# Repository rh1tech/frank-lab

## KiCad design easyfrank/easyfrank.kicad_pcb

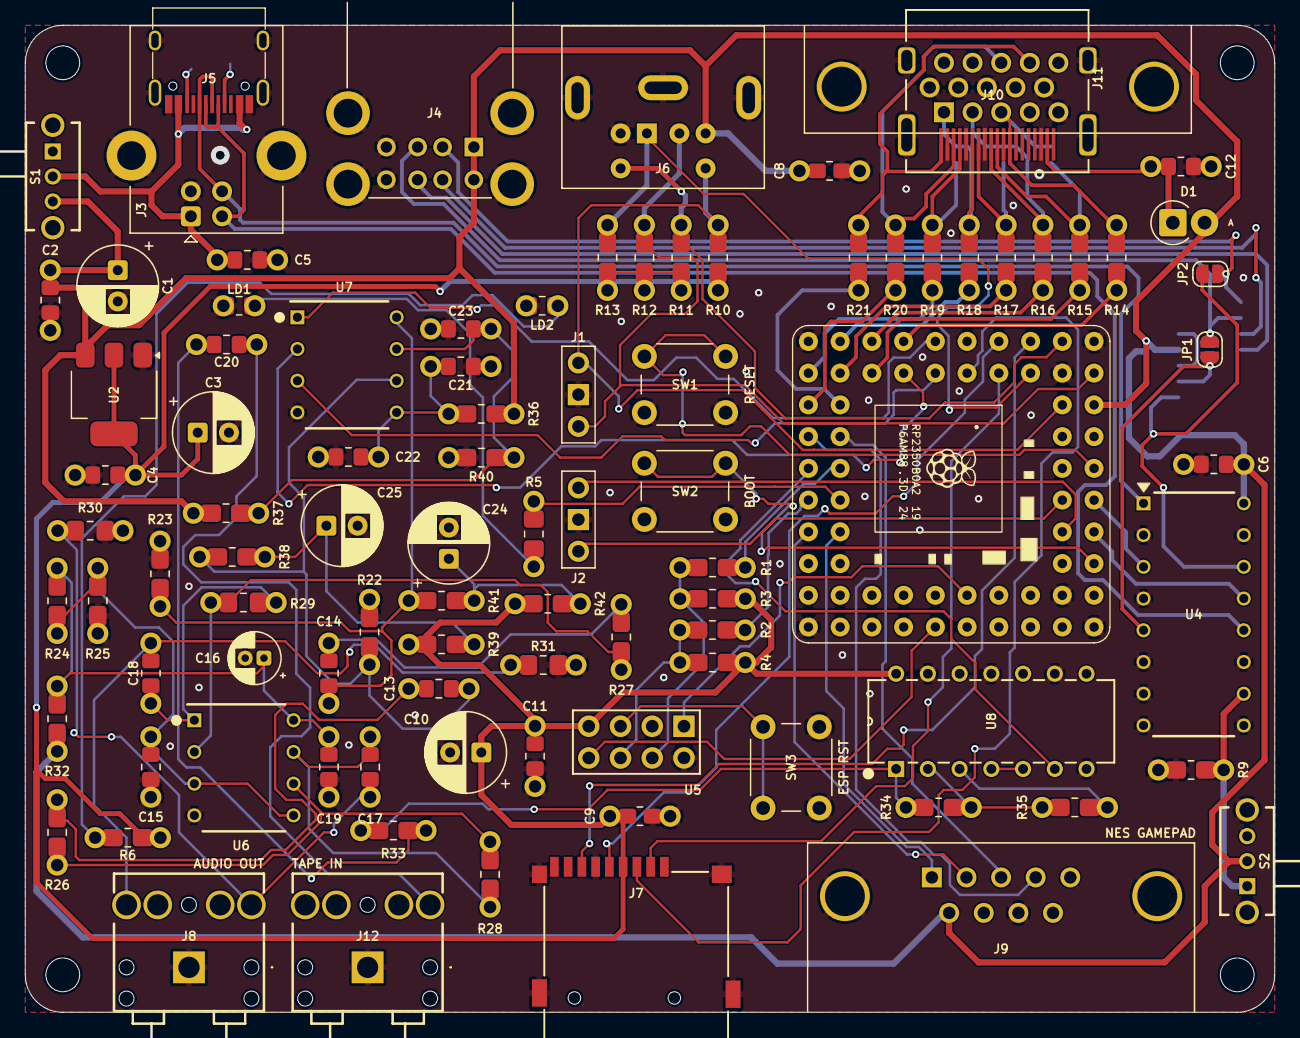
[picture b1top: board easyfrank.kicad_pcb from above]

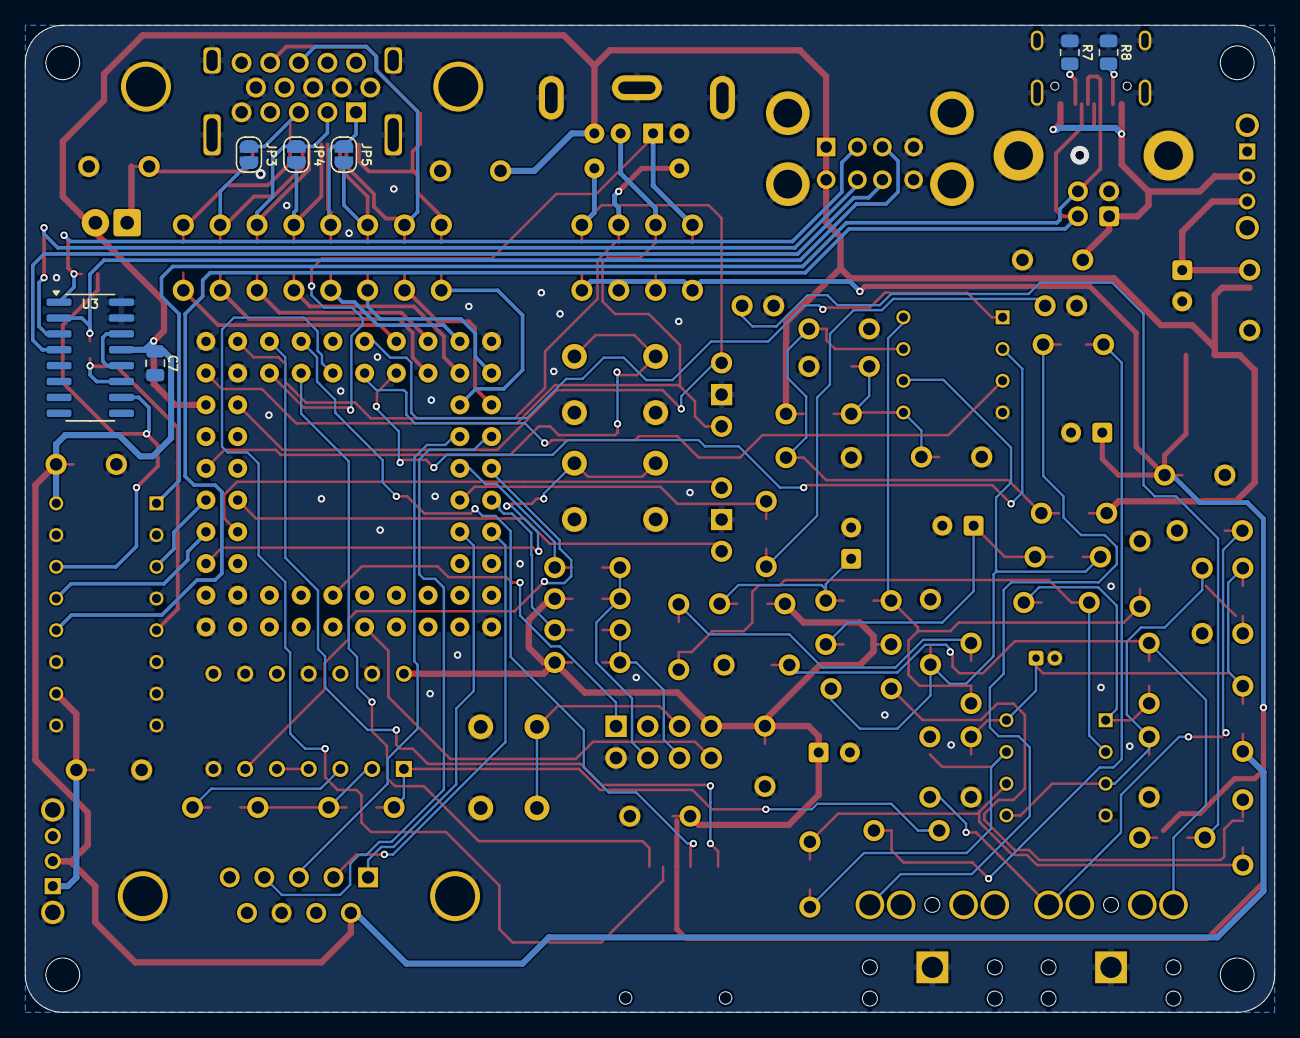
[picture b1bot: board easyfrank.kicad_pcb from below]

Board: 2 copper layers, 100.0 x 79.0 mm, 104 parts (7 on the bottom side), 87 nets.

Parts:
C1, C3, C10, C24, C25: 100u; C_Radial_D6.3mm_P2.50mm
C2, C4, C6, C8, C9, C11, C12, C19, C20, C22: 100n; Combined_0805_CR
C5, C13, C14, C15, C17, C18, C21, C23: 10u; Combined_0805_CR
C7: 4.7u; C_0805_2012Metric
C16: 10u; CP_Radial_D4.0mm_P1.50mm
D1: 1N5819; D_SOD81_P2.54mm_Vertical_AnodeUp
H1, H2, H3, H4: Hole 2.7mm; MountingHole_2.7mm
J1: UART; PinSocket_1x03_P2.54mm_Vertical
J2: Debug; PinSocket_1x03_P2.54mm_Vertical
J3: USB_B; USB_B_Horizontal
J4: SS-52100-004; USB_A_Stacked
J5: USB4215-03-A; USB_C_Receptacle
J6: MDC-036; MiniDIN_6pin_Female
J7: 104031-0811; MicroSD_SMD_Long
J8: SJ1-3525N Green; AudioJack_3.5mm_SJ1-3525N_Green
J9: D-SUB 9 Male; DSUB-9_Male_TopMount
J10: DC3RX19JA2; HDMI_Female
J11: D-SUB 15 Female; DSUB-15_Female
J12: SJ1-3525N Red; AudioJack_3.5mm_SJ1-3525N_Red
JP1, JP2, JP3, JP4, JP5: Jumper (Solder); SolderJumper_2Pin
LD1: Blue; Combined_0805_LED
LD2: Green; Combined_0805_LED
R1, R2, R5, R6, R10, R11, R12, R13: 1K; Combined_0805_RE
R3, R4, R9, R24, R25, R26, R27, R40: 10K; Combined_0805_RE
R7, R8: 5.1K; R_0805_2012Metric
R14, R15, R16, R17, R18, R19, R20, R21: 220R; Combined_0805_RE
R22, R23: 2.2K; Combined_0805_RE
R28, R29: 47K; Combined_0805_RE
R30, R31: 20K; Combined_0805_RE
R32, R36, R39, R42: 100R; Combined_0805_RE
R33: 4.7K; Combined_0805_RE
R34, R35: 100K; Combined_0805_RE
R37: 51K; Combined_0805_RE
R38, R41: 470R; Combined_0805_RE
S1, S2: SK12D07VG3NS; Switch_Slide_SK12D07VG3NS
SW1: Reset; SW_PUSH_6mm_H5mm
SW2: Boot; SW_PUSH_6mm_H5mm
SW3: ESP01 Reset; SW_PUSH_6mm_H5mm
U1: Pimoroni PGA2350; PGA2350
U2: AMS1117-3.3; SOT-223-3_TabPin2
U3: MW7211A; SOP-16_3.9x9.9mm_P1.27mm
U4: 74HC4052; 74HC4052N
U5: ESP-01v090; ESP-01S
U6: LM358; DIP-8_W7.94mm_P2.54mm
U7: TDA1545A; DIP-8_W7.94mm_P2.54mm
U8: CD4069UBE

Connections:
+3V3: C3.1, C4.2, C9.2, C10.1, C11.2, J7.4 (VDD), R3.2, R4.2, R6.2, R10.2, R11.2, R12.2, R13.2, R39.1, R42.1, U2.2 (VO), U5.7 (VCC), U8.14 (VDD)
/Audio/AMP_OUTL: C17.2, J8.2 (TIP), R30.2
/Audio/AMP_OUTR: C18.2, J8.3 (RING), R31.2
/Audio/TDA_L: C13.1, R22.1, R38.2, U7.6 (IOL)
/Audio/TDA_R: C14.1, R23.1, R41.1, U7.8 (IOR)
/CDDAT3/GP5: J7.2 (DAT3/CD), U1.5 (GP5)
/CLKN/GP12: R14.2, U1.12 (GP12)
/CLKP/GP13: R15.2, U1.13 (GP13)
/CLK/GP6: J7.5 (CLK), U1.6 (GP6)
/CMD/GP7: J7.3 (CMD), U1.7 (GP7)
/D0N/GP14: R16.2, U1.14 (GP14)
/D0P/GP15: R17.2, U1.15 (GP15)
/D1N/GP16: R18.2, U1.16 (GP16)
/D1P/GP17: R19.2, U1.17 (GP17)
/D2N/GP18: R20.2, U1.19 (GP18)
/D2P/GP19: R21.2, U1.20 (GP19)
/DAT0/GP4: J7.7 (DAT0), U1.4 (GP4)
/DATA1/GP26: J9.2, U1.27 (GP26)
/DATA2/GP27: J9.1, U1.28 (GP27)
/DM: U1.53 (USB_DM), U4.13 (1Z)
/DP: U1.54 (USB_DP), U4.3 (2Z)
/EGP0/GP24: R2.2, U1.25 (GP24)
/EGP2/GP23: R1.2, U1.24 (GP23)
/ESP01S/GPIO0: R2.1, R4.1, U5.6 (GPIO0)
/ESP01S/GPIO2: R1.1, R3.1, U5.4 (GPIO2)
/J3/GP21: J9.3, U1.22 (GP21)
/J4/GP20: J9.4, U1.21 (GP20)
/KB_CLK/GP2: J6.5, R11.1, U1.2 (GP2)
/KB_DATA/GP3: J6.1, R13.1, U1.3 (GP3)
/LOAD_IN/GP22: U1.23 (GP22), U8.6 (I=*C)
/MS_CLK/GP0: J1.1, J6.6, R10.1, U1.61 (GP0)
/MS_DATA/GP1: J1.3, J6.2, R12.1, U1.62 (GP1)
/PGA2350/BOOTSEL: SW2.1, U1.51 (BOOTSEL)
/PGA2350/RUN: SW1.1, U1.56 (RUN)
/PGA2350/SWCLK: J2.3, U1.55 (SWCLK)
/PGA2350/SWDIO: J2.1, U1.52 (SWDIO)
/RX/GP38: U1.40 (GP38), U5.8 (URXD)
/TDA_DATA/GP9: U1.9 (GP9), U7.3 (DATA)
/TDA_LRCK/GP11: U1.11 (GP11), U7.2 (WS)
/TDA_SCLK/GP10: U1.10 (GP10), U7.1 (BCK)
/TX/GP39: U1.41 (GP39), U5.1 (UTXD)
/Tape In/TAPE: C20.2, J12.2 (TIP)
/USB/DI+: J3.3 (D+), J5.6 (DP1), J5.8 (DP2), U4.1 (2Y0)
/USB/DI-: J3.2 (D-), J5.5 (DN2), J5.7 (DN1), U4.12 (1Y0)
/USB/DS+: JP1.1 (A), U3.11 (DPU), U4.5 (2Y1)
/USB/DS-: JP2.1 (A), U3.10 (DMU), U4.14 (1Y1)
/USB/DU1+: J4.3 (D1+), JP1.2 (B), U3.2 (DP0)
/USB/DU1-: J4.2 (D1-), JP2.2 (B), U3.1 (DM0)
/USB/DU2+: J4.7 (D2+), U3.4 (DP1)
/USB/DU2-: J4.6 (D2-), U3.3 (DM1)
/USB/VBUS_IN: C5.1, J3.1 (VBUS), J5.2 (VBUS), J5.11 (VBUS), S1.2
/Video Out/VGA_B: J10.12 (CLKN), J11.3, JP3.1 (A), R14.1
/Video Out/VGA_BH: J10.10 (CLKP), JP3.2 (B), R15.1
/Video Out/VGA_G: J10.9 (D0N), J11.2, JP4.1 (A), R16.1
/Video Out/VGA_GH: J10.7 (D0P), JP4.2 (B), R17.1
/Video Out/VGA_HS: J10.3 (D2N), J11.13, R20.1
/Video Out/VGA_R: J10.6 (D1N), J11.1, JP5.1 (A), R18.1
/Video Out/VGA_RH: J10.4 (D1P), JP5.2 (B), R19.1
/Video Out/VGA_VS: J10.1 (D2P), J11.14, R21.1
GND: C1.2, C2.1, C3.2, C4.1, C5.2, C6.1, C7.2, C8.2, C9.1, C10.2, C11.1, C12.2, C15.1, C16.2, C19.1, C21.2, C22.2, C23.1, C24.2, C25.2, J1.2, J2.2, J3.4 (GND), J3.SH (Shield), J4.4 (GND1), J4.8 (GND2), J4.SH (Shield), J5.1 (GND), J5.12 (GND), J5.13 (SHIELD), J6.3, J7.6 (VSS), J8.1 (SLEEVE), J9.8, J10.2 (G_D2), J10.5 (G_D1), J10.8 (G_D0), J10.11 (G_CLK), J10.17 (G_DDC/CEC), J10.20 (SHIELD1), J10.21 (SHIELD2), J10.22 (SHIELD3), J10.23 (SHIELD4), J11.0, J11.5, J11.6, J11.7, J11.8, J11.10, J12.1 (SLEEVE), LD1.1 (K), LD2.1 (K), R7.1, R8.1, R9.1, R22.2, R23.2, R25.1, R30.1, R31.1, R40.1, S2.4 (MH1), S2.5 (MH2), SW1.2, SW2.2, SW3.2, U1.1 (GND), U1.18 (GND), U1.33 (GND), U1.48 (GND), U2.1 (GND), U3.15 (GND), U3.16 (GND), U4.2 (2Y2), U4.4 (2Y3), U4.6 (~E), U4.7 (VEE), U4.8 (GND), U4.9 (S1), U4.11 (1Y3), U4.15 (1Y2), U5.2 (GND), U6.4 (V-), U7.4 (GND), U8.7 (VSS), U8.9 (D14), U8.11 (E), U8.13 (F)
GP25: R5.2, U1.26 (GP25)
unnamed: C13.2, R26.2
unnamed: C14.2, R27.2
unnamed: C17.1, R28.1, U6.7
unnamed: C18.1, R29.1, U6.1
unnamed: C20.1, R33.2
unnamed: C24.1, R41.2, R42.2
unnamed: C25.1, R38.1, R39.2
unnamed: C12.1, D1.1 (K), J10.18 (+5V)
unnamed: J5.4 (CC1), R7.2
unnamed: J5.10 (CC2), R8.2
unnamed: LD1.2 (A), R5.1
unnamed: LD2.2 (A), R6.1
unnamed: U3.12 (VD33), U3.14 (VD3)
unnamed: R9.2, S2.1, U4.10 (S0)
unnamed: SW3.1, U5.5 (RST)
unnamed: C15.2, R24.1, R25.2, U6.3 (+), U6.5 (+)
unnamed: R27.1, R29.2, U6.2 (-)
unnamed: R26.1, R28.2, U6.6 (-)
unnamed: C16.1, C19.2, R24.2, R32.2, U6.8 (V+)
unnamed: C23.2, R37.2, R40.2, U7.7 (IREF)
unnamed: C21.1, C22.1, R36.1, U7.5 (VDD)
unnamed: R33.1, R34.2, U8.1 (A)
unnamed: R35.1, U8.3 (B)
unnamed: U8.4 (H=*B), U8.5 (C)
unnamed: R34.1, R35.2, U8.2 (G-*A)
VBUS: C1.1, C2.2, C6.2, C7.1, C8.1, D1.2 (A), J4.1 (VBUS1), J4.5 (VBUS2), J6.4, J9.6, R32.1, R36.2, R37.1, S1.3, S2.2, U1.60 (VBUS), U2.3 (VI), U3.13 (VDD5), U4.16 (VCC)

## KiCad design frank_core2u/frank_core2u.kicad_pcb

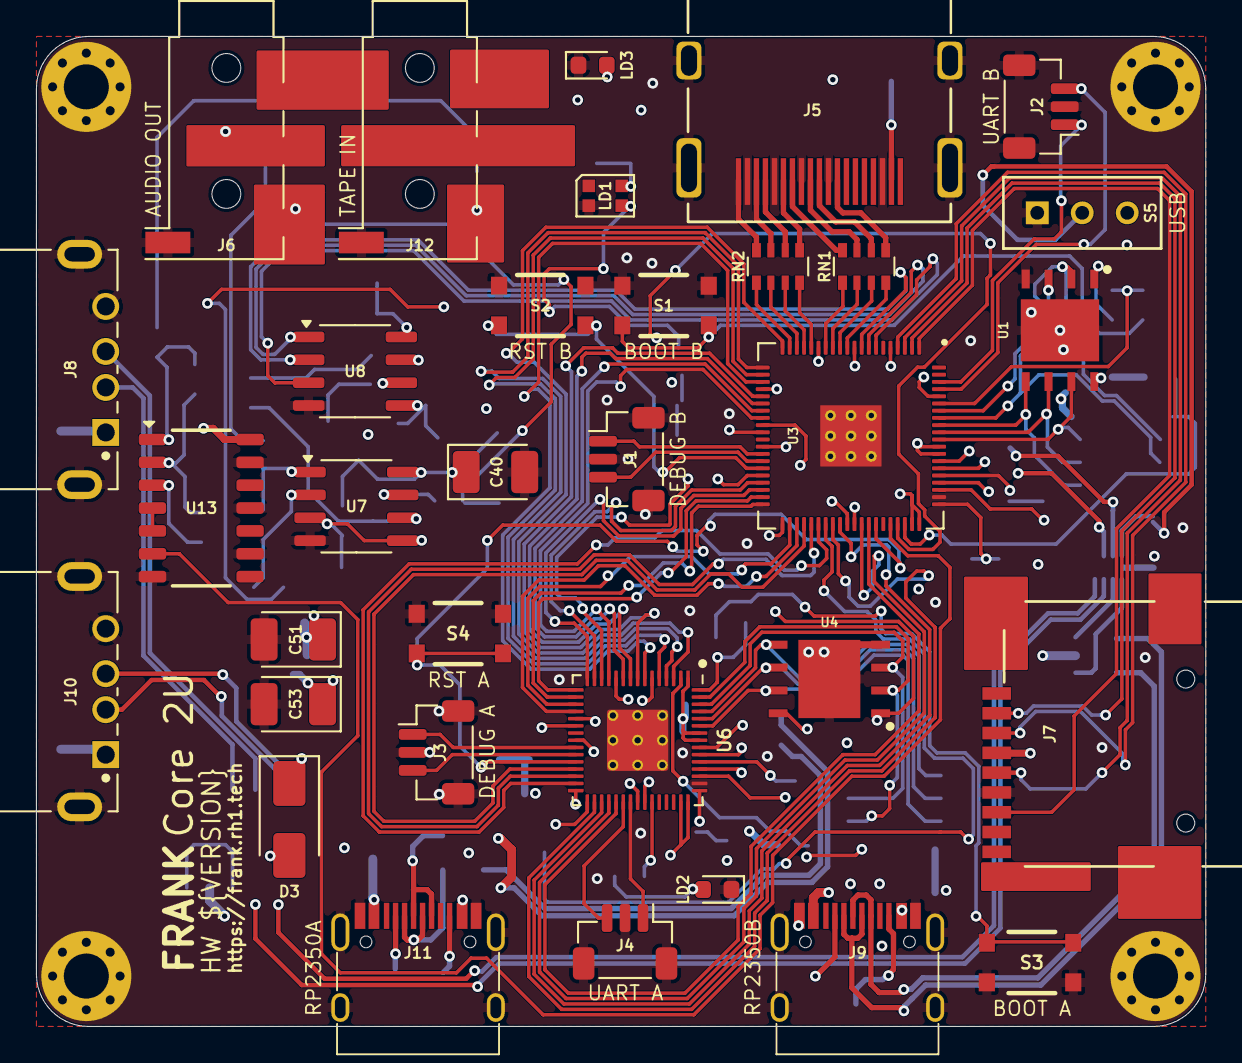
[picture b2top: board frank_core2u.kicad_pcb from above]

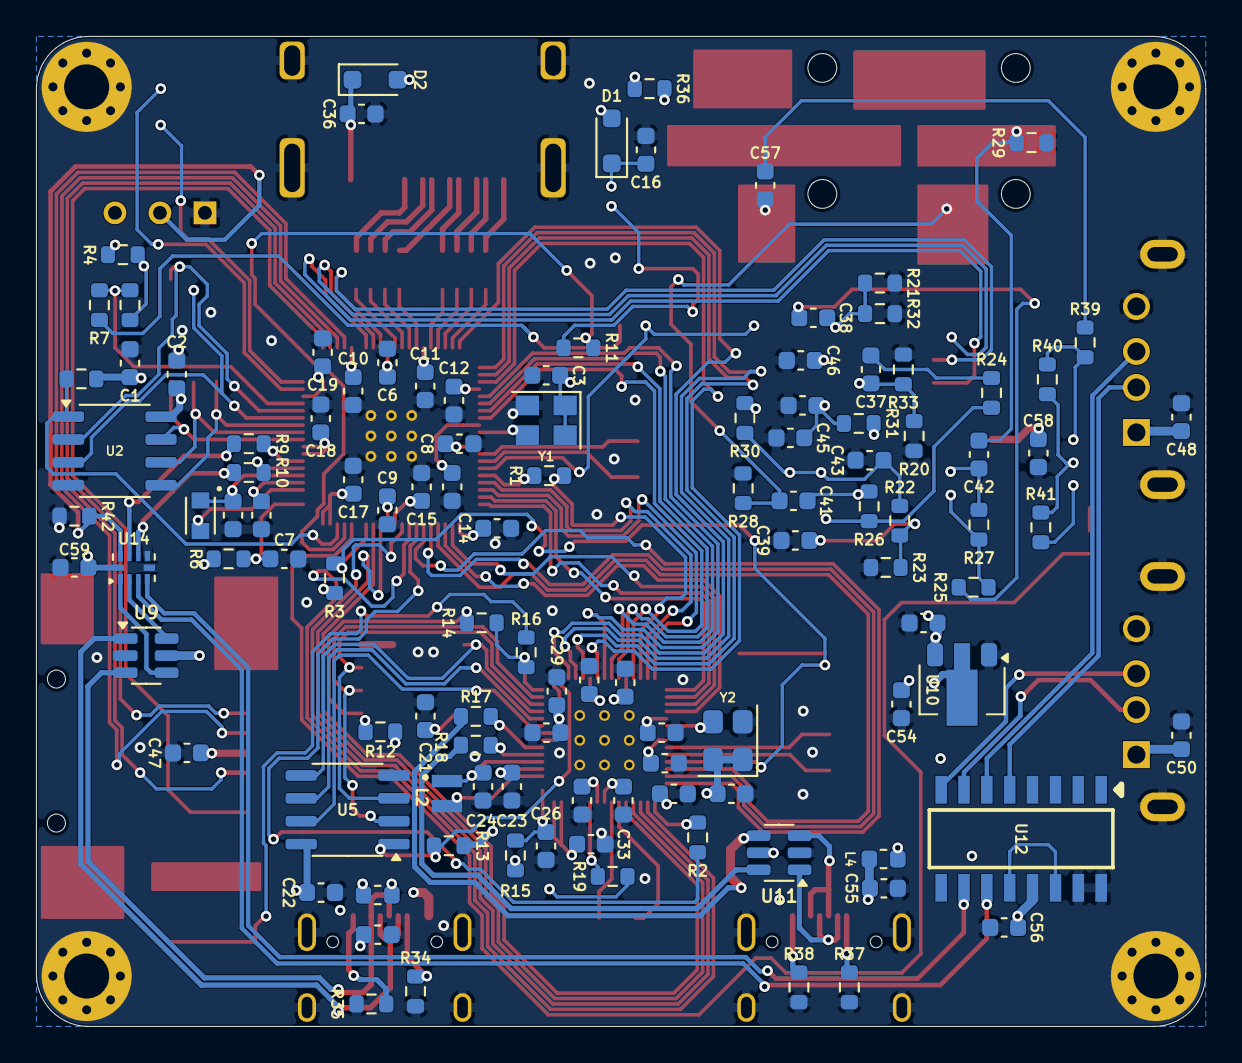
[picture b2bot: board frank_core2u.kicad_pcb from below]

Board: 4 copper layers, 65.0 x 55.0 mm, 150 parts (113 on the bottom side), 144 nets.

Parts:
C1, C2, C3, C6, C9, C10, C11, C12, C13, C14, C15, C16, C17, C18, C19, C20, C21, C22, C25, C28, C29, C30, C31, C32, C33, C34, C35, C36, C43, C45, C47, C48, C49, C50, C52, C54, C55, C59: 100n; C_0603_1608Metric
C4, C5, C7, C8, C23, C24, C26, C27, C56: 4.7u; C_0603_1608Metric
C37, C38, C39, C41, C42, C44, C46: 10u; C_0603_1608Metric
C40: 10u; CP_EIA-3528-12_Kemet-T
C51, C53: 22u; CP_EIA-3528-12_Kemet-T
C57, C58: 100nF; C_0603_1608Metric
D1, D2: 1N5819WS; D_SOD-323
D3: SS34; D_SMA
H1, H2, H3, H4: MountingHole; MountingHole_2.5mm_Pad_Via
J1, J3: Debug; JST_SH_1x03_P1.00mm_Vertical
J2, J4: UART; JST_SH_1x03_P1.00mm_Vertical
J5: DC3RX19JA2; HDMI_Female
J6: PJ-320D; AudioJack_3.5mm_PJ320D_AudioOut
J7: 104031-0811; MicroSD_SMD_Long
J8, J10: 676430910; USB_A_Short
J9, J11: USB4215-03-A; USB_C_Receptacle
J12: PJ-320D; AudioJack_3.5mm_PJ320D_TapeIn
L1: 3.3u; L_Murata_LQH2MCN_2.0x1.6mm
L2: 3.3u; L_AOTA-B201610_2.0x1.6mm
L3, L4: 330R; L_0603_1608Metric
LD1: WS2812B-2020; LED_WS2812B-2020_PLCC4_2.0x2.0mm
LD2: Blue; LED_0603_1608Metric
LD3: Green; LED_0603_1608Metric
R1, R2, R6, R15: 33R; R_0603_1608Metric
R3, R4, R5, R12, R13, R20, R21, R22, R23, R24, R25, R42: 10K; R_0603_1608Metric
R7, R16, R19, R36: 1K; R_0603_1608Metric
R8, R14: 0R; R_0603_1608Metric
R9, R10, R17, R18: 27R; R_0603_1608Metric
R11: 330R; R_0603_1608Metric
R26, R27: 47K; R_0603_1608Metric
R28, R29: 20K; R_0603_1608Metric
R30, R31: 100R; R_0603_1608Metric
R32, R33: 470R; R_0603_1608Metric
R34, R35, R37, R38: 5.1K; R_0603_1608Metric
R39: 4.7K; R_0603_1608Metric
R40, R41: 100K; R_0603_1608Metric
RN1, RN2: 270R; R_Array_4x0603
S1, S3: RP Boot; SW_SPST_KMR2
S2, S4: RP Reset; SW_SPST_KMR2
S5: SS12D00; Switch_Slide_SS12D00
U1, U4: W25Q128JVPIQ; WSON-8-1EP_6x5mm_P1.27mm_EP3.45x4.35mm
U2, U5: ESP-PSRAM64H; SOIC-8_3.9x4.9mm_P1.27mm
U3: RP2350B; QFN-80-1EP_10x10mm_P0.4mm_EP3.4x3.4mm
U6: RP2350; QFN-60-1EP_7x7mm_P0.4mm_EP3.4x3.4mm
U7: LM358; SOIC-8_3.9x4.9mm_P1.27mm
U8: TDA1387T; SOIC-8_3.9x4.9mm_P1.27mm
U9, U11: USBLC6-2SC6; SOT-23-6
U10: AMS1117-3.3; SOT-89-3
U12: MW7211A; SOIC127P600X175-16N
U13: CD4069UBM; SOIC-14_3.9x8.7mm_P1.27mm
U14: TS3USB221RSER; Texas_R-PUQFN-N10
Y1: ASE-12MHz; Oscillator_SMD_3225-4Pin_3.2x2.5mm
Y2: ASE-12MHz; Oscillator_SMD_Abracon_ASE-4Pin_3.2x2.5mm

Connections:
+1V1: C5.1, C6.1, C8.1, C9.1, L1.1, U3.10 (DVDD), U3.32 (DVDD), U3.51 (DVDD), U3.65 (VREG_FB)
+1V1_A: C24.1, C25.1, C27.1, C28.1, L2.1, U6.6 (DVDD), U6.23 (DVDD), U6.39 (DVDD), U6.50 (VREG_FB)
+3V3: C1.1, C2.1, C3.1, C4.1, C10.1, C11.1, C12.1, C13.1, C14.1, C15.1, C17.1, C18.1, C19.1, C20.1, C21.1, C22.1, C23.1, C29.1, C30.1, C31.1, C32.1, C33.1, C34.1, C35.1, C47.2, C53.1, C54.2, C58.1, C59.2, J7.4 (VDD), R3.2, R4.2, R5.2, R6.1, R12.2, R13.2, R15.1, R36.2, S5.3, U1.8 (VCC), U2.8 (VCC), U3.5 (IOVDD), U3.15 (IOVDD), U3.24 (IOVDD), U3.29 (IOVDD), U3.41 (IOVDD), U3.50 (IOVDD), U3.59 (ADC_AVDD), U3.60 (IOVDD), U3.64 (VREG_VIN), U3.68 (USB_OTP_VDD), U3.69 (QSPI_IOVDD), U3.76 (IOVDD), U4.8 (VCC), U5.8 (VCC), U6.1 (IOVDD), U6.11 (IOVDD), U6.20 (IOVDD), U6.30 (IOVDD), U6.38 (IOVDD), U6.44 (ADC_AVDD), U6.45 (IOVDD), U6.49 (VREG_VIN), U6.53 (USB_OTP_VDD), U6.54 (QSPI_IOVDD), U10.2 (VO), U13.14 (VDD), U14.10 (VCC), Y1.1 (EN), Y1.4 (Vdd), Y2.1 (EN), Y2.4 (Vdd)
/HDMI/CLKN/GPIO12: RN1.4 (R4.1), U3.11 (GPIO12)
/HDMI/CLKP/GPIO13: RN1.3 (R3.1), U3.12 (GPIO13)
/HDMI/D0N/GPIO14: RN1.2 (R2.1), U3.13 (GPIO14)
/HDMI/D0P/GPIO15: RN1.1 (R1.1), U3.14 (GPIO15)
/HDMI/D1N/GPIO16: RN2.4 (R4.1), U3.16 (GPIO16)
/HDMI/D1P/GPIO17: RN2.3 (R3.1), U3.17 (GPIO17)
/HDMI/D2N/GPIO18: RN2.2 (R2.1), U3.18 (GPIO18)
/HDMI/D2P/GPIO19: RN2.1 (R1.1), U3.19 (GPIO19)
/RP2350A/BOOT: R16.2, S3.1, S3.3
/RP2350A/GPIO0: R13.1, U5.1 (~CE), U6.2 (GPIO0)
/RP2350A/GPIO19: R2.1, U6.31 (GPIO19)
/RP2350A/QSPI_SCLK: U4.6 (CLK), U5.6 (SCLK), U6.56 (QSPI_SCLK)
/RP2350A/QSPI_SD0: U4.5 (DI_(IO0)), U5.5 (SI/SIO), U6.57 (QSPI_SD0)
/RP2350A/QSPI_SD1: U4.2 (DO_(IO1)), U5.2 (SO/SIO), U6.59 (QSPI_SD1)
/RP2350A/QSPI_SD2: U4.3 (~WP_(IO2)), U5.3 (SIO2), U6.58 (QSPI_SD2)
/RP2350A/QSPI_SD3: U4.7 (~HOLD_OR_/RESET_(IO3)), U5.7 (SIO3), U6.55 (QSPI_SD3)
/RP2350A/QSPI_SS: R14.1, R16.1, U6.60 (QSPI_SS)
/RP2350A/SWCLK: J3.3, U6.24 (SWCLK)
/RP2350A/SWD: J3.1, U6.25 (SWD)
/RP2350A/VREG_AVDD: C26.1, R15.2, U6.46 (VREG_AVDD)
/RP2350A/VREG_LX: L2.2, U6.48 (VREG_LX)
/RP2350A/XIN: U6.21 (XIN), Y2.3 (OUT)
/RP2350A/D+: R17.1, U11.4 (I/O2)
/RP2350A/D-: R18.1, U11.6 (I/O1)
/RP2350B/BOOT: R7.2, S1.1, S1.3
/RP2350B/GPIO28: R1.2, U3.36 (GPIO28)
/RP2350B/GPIO45: U3.56 (GPIO45_ADC5), U13.6 (I=*C)
/RP2350B/GPIO47: R5.1, U2.1 (~CE), U3.58 (GPIO47_ADC7)
/RP2350B/QSPI_SCLK: U1.6 (CLK), U2.6 (SCLK), U3.71 (QSPI_SCLK)
/RP2350B/QSPI_SD0: U1.5 (DI_(IO0)), U2.5 (SI/SIO), U3.72 (QSPI_SD0)
/RP2350B/QSPI_SD1: U1.2 (DO_(IO1)), U2.2 (SO/SIO), U3.74 (QSPI_SD1)
/RP2350B/QSPI_SD2: U1.3 (~WP_(IO2)), U2.3 (SIO2), U3.73 (QSPI_SD2)
/RP2350B/QSPI_SD3: U1.7 (~HOLD_OR_/RESET_(IO3)), U2.7 (SIO3), U3.70 (QSPI_SD3)
/RP2350B/QSPI_SS: R7.1, R8.1, U3.75 (QSPI_SS)
/RP2350B/RUN: S2.1, S2.3, U3.35 (RUN)
/RP2350B/SWCLK: J1.3, U3.33 (SWCLK)
/RP2350B/SWD: J1.1, U3.34 (SWD)
/RP2350B/VREG_AVDD: C7.1, R6.2, U3.61 (VREG_AVDD)
/RP2350B/VREG_LX: L1.2, U3.63 (VREG_LX)
/RP2350B/XIN: U3.30 (XIN), Y1.3 (OUT)
/RP2350B/D+: R9.1, U14.8 (D+)
/RP2350B/D-: R10.1, U14.7 (D-)
/RP2350/20B/1A/D0: U3.20 (GPIO20), U6.3 (GPIO1)
/RP2350/21B/2A/D1: U3.21 (GPIO21), U6.4 (GPIO2)
/RP2350/22B/3A/D2: U3.22 (GPIO22), U6.5 (GPIO3)
/RP2350/23B/4A/D3: U3.23 (GPIO23), U6.7 (GPIO4)
/RP2350/24B/5A/D4: U3.25 (GPIO24), U6.8 (GPIO5)
/RP2350/25B/6A/D5: U3.26 (GPIO25), U6.9 (GPIO6)
/RP2350/26B/7A/D6: U3.27 (GPIO26), U6.10 (GPIO7)
/RP2350/27B/8A/D7: U3.28 (GPIO27), U6.12 (GPIO8)
/RP2350/28B/9A/CLK: R1.1, U6.13 (GPIO9)
/RP2350/29B/10A/VALID: U3.37 (GPIO29), U6.14 (GPIO10)
/RP2350/30B/11A/D0: U3.38 (GPIO30), U6.15 (GPIO11)
/RP2350/31B/12A/D1: U3.39 (GPIO31), U6.16 (GPIO12)
/RP2350/32B/13A/D2: U3.40 (GPIO32), U6.17 (GPIO13)
/RP2350/33B/14A/D3: U3.42 (GPIO33), U6.18 (GPIO14)
/RP2350/34B/15A/D4: U3.43 (GPIO34), U6.19 (GPIO15)
/RP2350/35B/16A/D5: U3.44 (GPIO35), U6.27 (GPIO16)
/RP2350/36B/17A/D6: U3.45 (GPIO36), U6.28 (GPIO17)
/RP2350/37B/18A/D7: U3.46 (GPIO37), U6.29 (GPIO18)
/RP2350/38B/19A/CLK: R2.2, U3.47 (GPIO38)
/RP2350/39B/20A/VALID: U3.48 (GPIO39), U6.32 (GPIO20)
/RP2350/40B/21A/FS: U3.49 (GPIO40_ADC0), U6.33 (GPIO21)
/RP2350/41B/22A/DB_MS: U3.52 (GPIO41_ADC1), U6.34 (GPIO22)
/RP2350/42B/23A/DB_SM: U3.53 (GPIO42_ADC2), U6.35 (GPIO23)
/RP2350/43B/RUNA/SR: R3.1, S4.1, S4.3, U3.54 (GPIO43_ADC3), U6.26 (RUN)
/SD/CDDAT3/GPIO5: J7.2 (DAT3/CD), U3.2 (GPIO5)
/SD/CLK/GPIO6: J7.5 (CLK), U3.3 (GPIO6)
/SD/CMD/GPIO7: J7.3 (CMD), U3.4 (GPIO7)
/SD/DAT0/GPIO4: J7.7 (DAT0), U3.1 (GPIO4)
/TDA Audio/AMP_OUTL: C41.2, J6.T, R28.2
/TDA Audio/AMP_OUTR: C42.2, J6.R, R29.2
/TDA Audio/TDA_L: C37.1, R20.1, R33.2, U8.6 (A_LEFT)
/TDA Audio/TDA_R: C38.1, R21.1, R32.1, U8.8 (A_RIGHT)
/TDA/DATA/GPIO9: U3.7 (GPIO9), U8.3 (DATA)
/TDA/LRCK/GPIO11: U3.9 (GPIO11), U8.2 (LRCK)
/TDA/SCLK/GPIO10: U3.8 (GPIO10), U8.1 (SCLK)
/Tape In/TAPE: C57.2, J12.T
/USB Master/S: R42.2, S5.2, U14.9 (S)
/USB Master/USB Hub/DM1: J10.2 (D-), U12.7 (DM3)
/USB Master/USB Hub/DM2: J8.2 (D-), U12.5 (DM2)
/USB Master/USB Hub/DM_IN: U12.10 (DMU), U14.4 (2D-)
/USB Master/USB Hub/DP1: J10.3 (D+), U12.8 (DP3)
/USB Master/USB Hub/DP2: J8.3 (D+), U12.6 (DP2)
/USB Master/USB Hub/DP_IN: U12.11 (DPU), U14.3 (2D+)
/USB Master/USB Multiplexer/D1+: U9.4 (I/O2), U14.1 (1D+)
/USB Master/USB Multiplexer/D1-: U9.6 (I/O1), U14.2 (1D-)
GND: C1.2, C2.2, C3.2, C4.2, C5.2, C6.2, C7.2, C8.2, C9.2, C10.2, C11.2, C12.2, C13.2, C14.2, C15.2, C16.2, C17.2, C18.2, C19.2, C20.2, C21.2, C22.2, C23.2, C24.2, C25.2, C26.2, C27.2, C28.2, C29.2, C30.2, C31.2, C32.2, C33.2, C34.2, C35.2, C36.2, C39.1, C40.2, C43.1, C44.2, C45.2, C46.2, C47.1, C48.2, C49.2, C50.2, C51.2, C52.1, C53.2, C54.1, C55.2, C56.2, C58.2, C59.1, H1.1 (1_1), H2.1 (1_1), H3.1 (1_1), H4.1 (1_1), J1.2, J2.2, J3.2, J4.2, J5.2 (G_D2), J5.5 (G_D1), J5.8 (G_D0), J5.11 (G_CLK), J5.17 (G_DDC/CEC), J5.20 (SHIELD1), J5.21 (SHIELD2), J5.22 (SHIELD3), J5.23 (SHIELD4), J6.S, J7.6 (VSS), J8.4 (GND), J8.5 (Shield), J9.1 (GND), J9.12 (GND), J9.13 (SHIELD), J10.4 (GND), J10.5 (Shield), J11.1 (GND), J11.12 (GND), J11.13 (SHIELD), J12.S, LD1.2 (VSS), LD2.1 (K), LD3.1 (K), R20.2, R21.2, R23.1, R28.1, R29.1, R32.2, R33.1, R34.1, R35.1, R37.1, R38.1, R42.1, S1.2, S1.4, S2.2, S2.4, S3.2, S3.4, S4.2, S4.4, S5.1, U1.4 (GND_1), U1.9 (GND_2), U2.4 (VSS), U3.62 (VREG_PGND), U3.81 (GND), U4.4 (GND_1), U4.9 (GND_2), U5.4 (VSS), U6.47 (VREG_PGND), U6.61 (GND), U7.4 (V-), U8.4 (AGND), U9.2 (GND), U10.1 (GND), U11.2 (GND), U12.15 (GND), U12.16 (GND), U13.7 (VSS), U13.9 (D14), U13.11 (E), U13.13 (F), U14.5 (GND), U14.6 (~OE), Y1.2 (GND), Y2.2 (GND)
unnamed: C37.2, R24.2
unnamed: C38.2, R25.2
unnamed: C41.1, R26.1, U7.7
unnamed: C42.1, R27.1, U7.1
unnamed: C49.1, J9.2 (VBUS), J9.11 (VBUS), L3.2
unnamed: C55.1, J11.2 (VBUS), J11.11 (VBUS), L4.2
unnamed: C57.1, R39.2
unnamed: C16.1, D1.1 (K), LD1.4 (VDD)
unnamed: C36.1, D2.1 (K), J5.18 (+5V)
unnamed: D3.2 (A), L4.1
unnamed: J2.1, U3.77 (GPIO0)
unnamed: J2.3, U3.78 (GPIO1)
unnamed: J4.1, U6.36 (GPIO24)
unnamed: J4.3, U6.37 (GPIO25)
unnamed: J5.12 (CLKN), RN1.5 (R4.2)
unnamed: J5.10 (CLKP), RN1.6 (R3.2)
unnamed: J5.9 (D0N), RN1.7 (R2.2)
unnamed: J5.7 (D0P), RN1.8 (R1.2)
unnamed: J5.6 (D1N), RN2.5 (R4.2)
unnamed: J5.4 (D1P), RN2.6 (R3.2)
unnamed: J5.3 (D2N), RN2.7 (R2.2)
unnamed: J5.1 (D2P), RN2.8 (R1.2)
unnamed: J9.4 (CC1), R34.2
unnamed: J9.10 (CC2), R35.2
unnamed: J9.5 (DN2), J9.7 (DN1), U9.1 (I/O1)
unnamed: J9.6 (DP1), J9.8 (DP2), U9.3 (I/O2)
unnamed: J11.4 (CC1), R37.2
unnamed: J11.10 (CC2), R38.2
unnamed: J11.5 (DN2), J11.7 (DN1), U11.1 (I/O1)
unnamed: J11.6 (DP1), J11.8 (DP2), U11.3 (I/O2)
unnamed: LD1.3 (DIN), R11.1
unnamed: LD2.2 (A), R19.1
unnamed: LD3.2 (A), R36.1
unnamed: R4.1, R8.2, U1.1 (~CS)
unnamed: R11.2, U3.57 (GPIO46_ADC6)
unnamed: R10.2, U3.66 (USB_DM)
unnamed: R9.2, U3.67 (USB_DP)
unnamed: R12.1, R14.2, U4.1 (~CS)
unnamed: R19.2, U6.40 (GPIO26_ADC0)
unnamed: R18.2, U6.51 (USB_DM)
unnamed: R17.2, U6.52 (USB_DP)
unnamed: C39.2, R22.1, R23.2, U7.3 (+), U7.5 (+)
unnamed: R25.1, R27.2, U7.2 (-)
unnamed: R24.1, R26.2, U7.6 (-)
unnamed: C40.1, C43.2, R22.2, R30.2, U7.8 (V+)
unnamed: C46.1, U8.7 (FLT)
unnamed: C44.1, C45.1, R31.1, U8.5 (VA)
unnamed: U12.12 (VD33), U12.14 (VD3)
unnamed: R39.1, R40.2, U13.1 (A)
unnamed: R41.1, U13.3 (B)
unnamed: U13.4 (H=*B), U13.5 (C)
unnamed: R40.1, R41.2, U13.2 (G-*A)
VBUS: C48.1, C50.1, C51.1, C52.2, C56.1, D1.2 (A), D2.2 (A), D3.1 (K), J8.1 (VBUS), J10.1 (VBUS), L3.1, R30.1, R31.2, U9.5 (VBUS), U10.3 (VI), U11.5 (VBUS), U12.13 (VDD5)

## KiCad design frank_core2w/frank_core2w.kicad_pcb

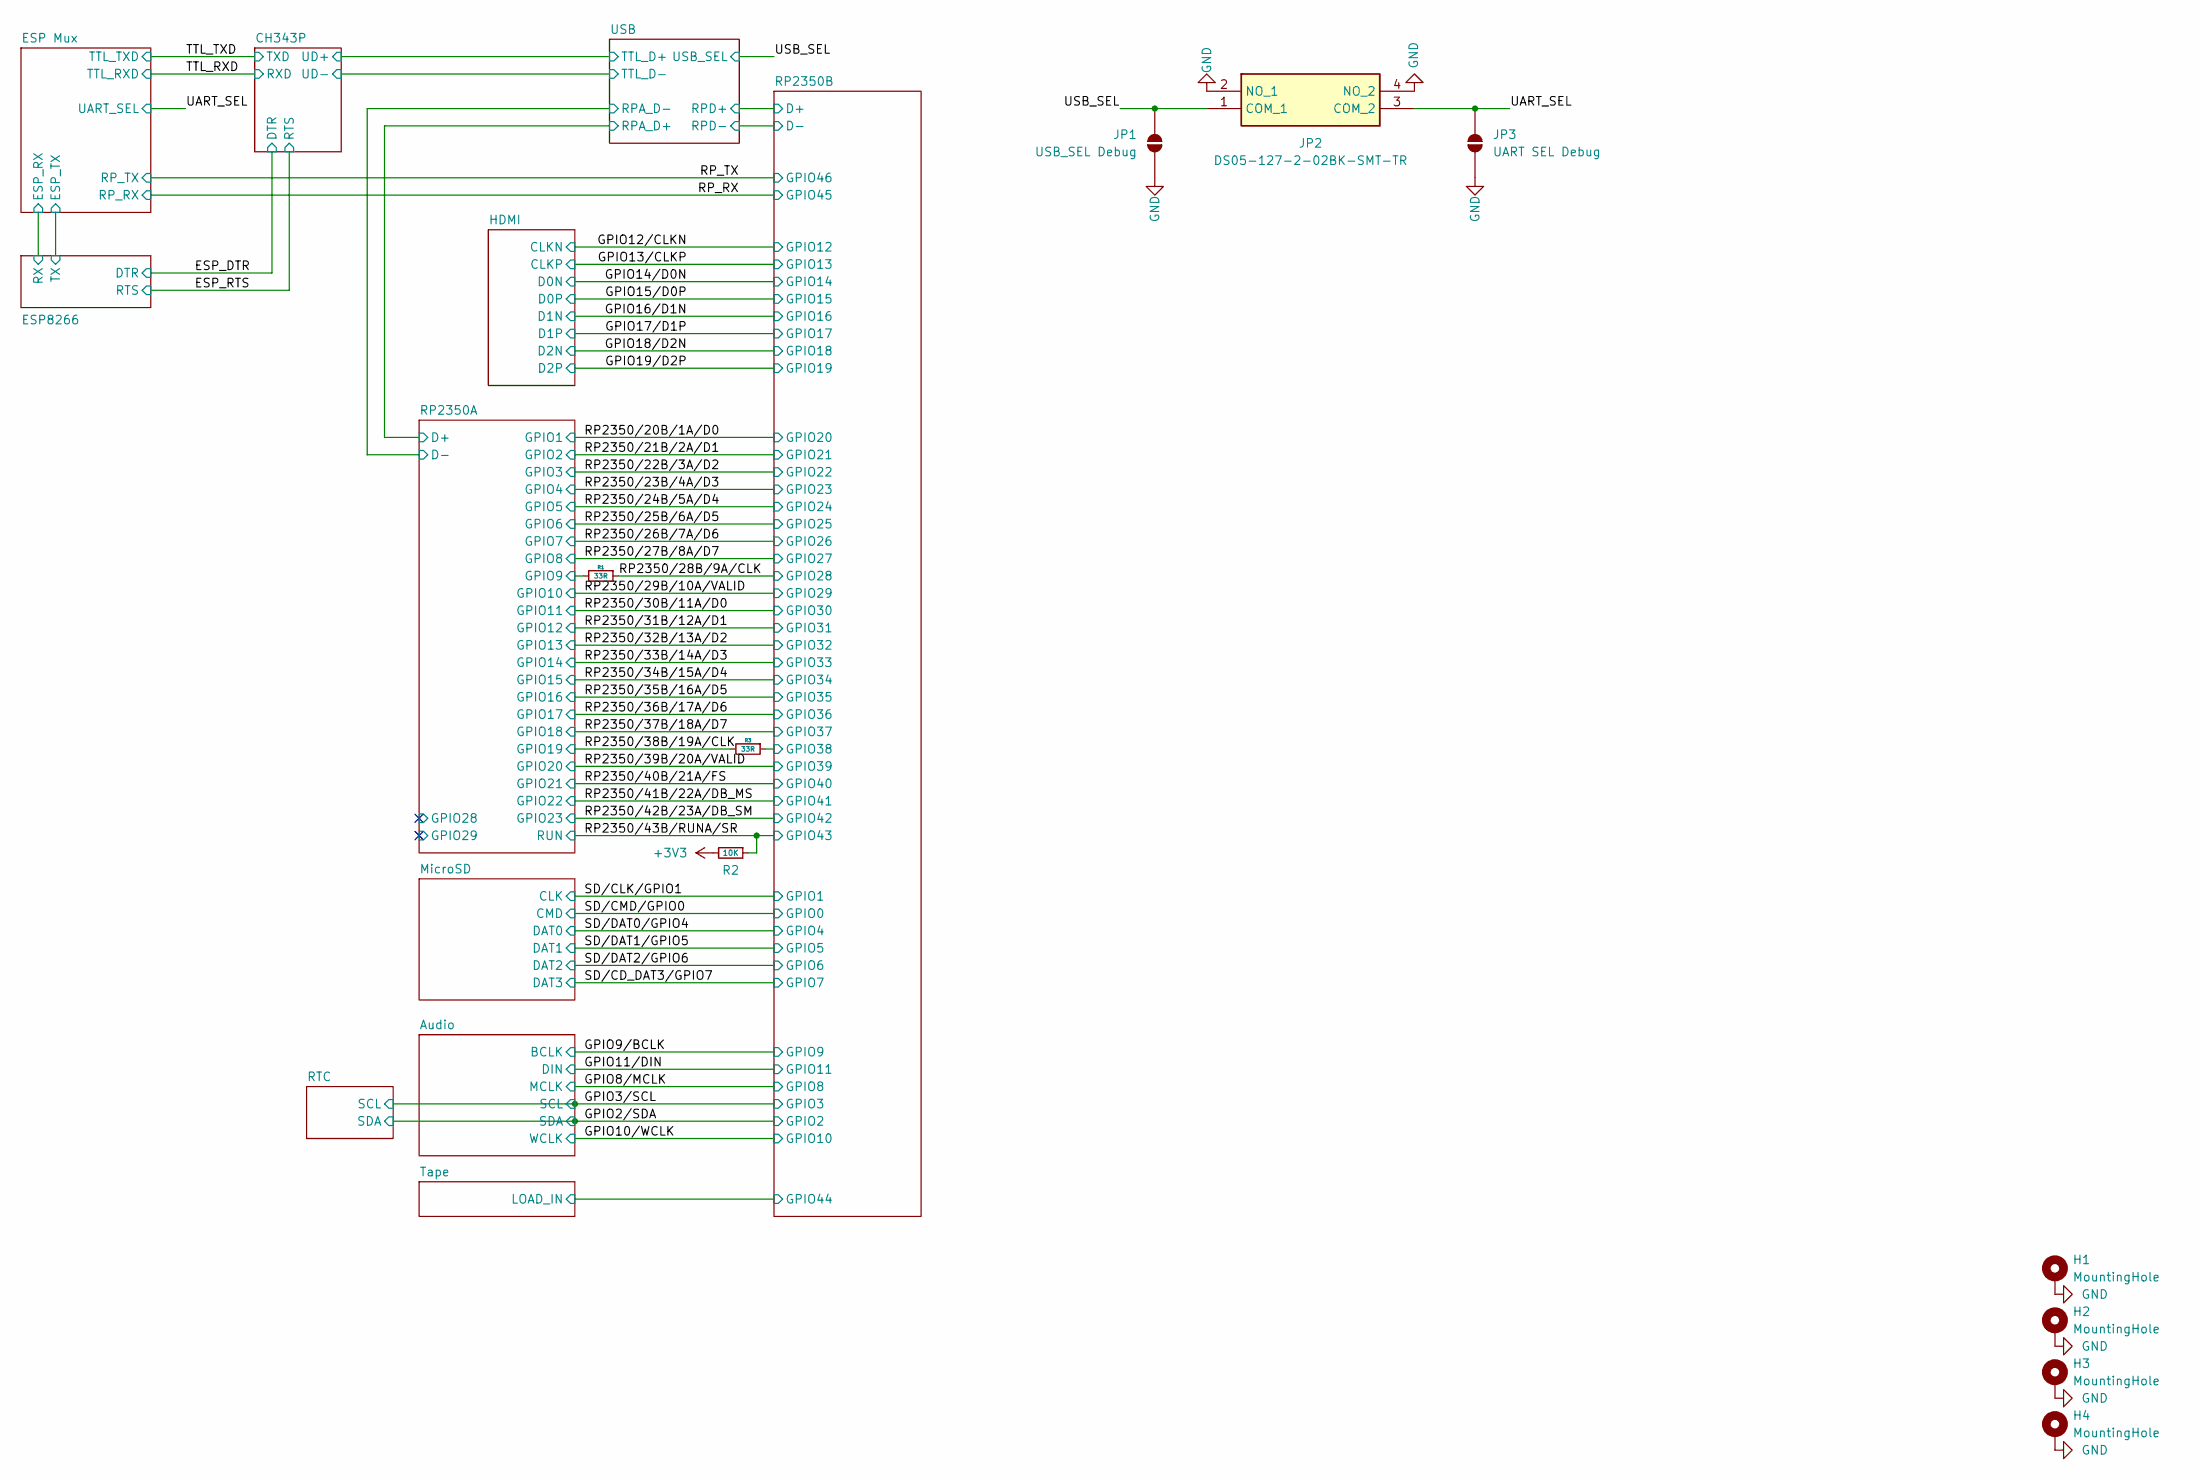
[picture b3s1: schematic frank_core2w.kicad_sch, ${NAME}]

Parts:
H1, H2, H3, H4: MountingHole; MountingHole_2.5mm_Pad_Via
JP1: USB_SEL Debug; SolderJumper-2_P1.3mm_Open_RoundedPad1.0x1.5mm
JP2: DS05-127-2-02BK-SMT-TR; SW_DS05-127-2-02BK-SMT-TR; Mouser Part Number 490-DS05127202BK-STR
JP3: UART SEL Debug; SolderJumper-2_P1.3mm_Open_RoundedPad1.0x1.5mm
R1, R3: 33R; R_0603_1608Metric; LCSC C23140
R2: 10K; R_0603_1608Metric; LCSC C2906982

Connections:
+3V3: R2.2; also elsewhere on the board
/RP2350A/GPIO9: R1.2; also elsewhere on the board
/RP2350B/GPIO38: R3.1; also elsewhere on the board
/RP2350/28B/9A/CLK: R1.1; also elsewhere on the board
/RP2350/38B/19A/CLK: R3.2; also elsewhere on the board
/RP2350/43B/RUNA/SR: R2.1; also elsewhere on the board
/UART_SEL: JP2.3 (COM_2), JP3.2 (B); also elsewhere on the board
/USB_SEL: JP1.2 (B), JP2.1 (COM_1); also elsewhere on the board
GND: H1.1 (1_1), H2.1 (1_1), H3.1 (1_1), H4.1 (1_1), JP1.1 (A), JP2.2 (NO_1), JP2.4 (NO_2), JP3.1 (A); also elsewhere on the board
